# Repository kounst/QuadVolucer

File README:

>QuadVolucer

QuadVolucer is a Quadcopter project basend on the STM32 Microcontroller. It uses a ITG-3200 3-axis gyroskope.

The aim of this project is not to develop a Copter which is as stable as possible but to leave control to the pilot. Therefore control is HH only.
To archive this no ACCs are needed. There is a footprint for a 3-axis ACC on the PCB though. So angular control could be implemented but I'm propably not going to do so.

>canBLC

canBLC is a motor controller for BLDC motors. It is meant to be used with multicopters like the QuadVolucer. As an interface it will support I2C, PWM and of cause high speed CAN.

	status:	- Hardware design is finished 
		- Software basic features working (only CAN support)

	todo:	- extensive testing
		- testing on the QuadVolucer :-)
		- implementation of PWM and I2C interface.

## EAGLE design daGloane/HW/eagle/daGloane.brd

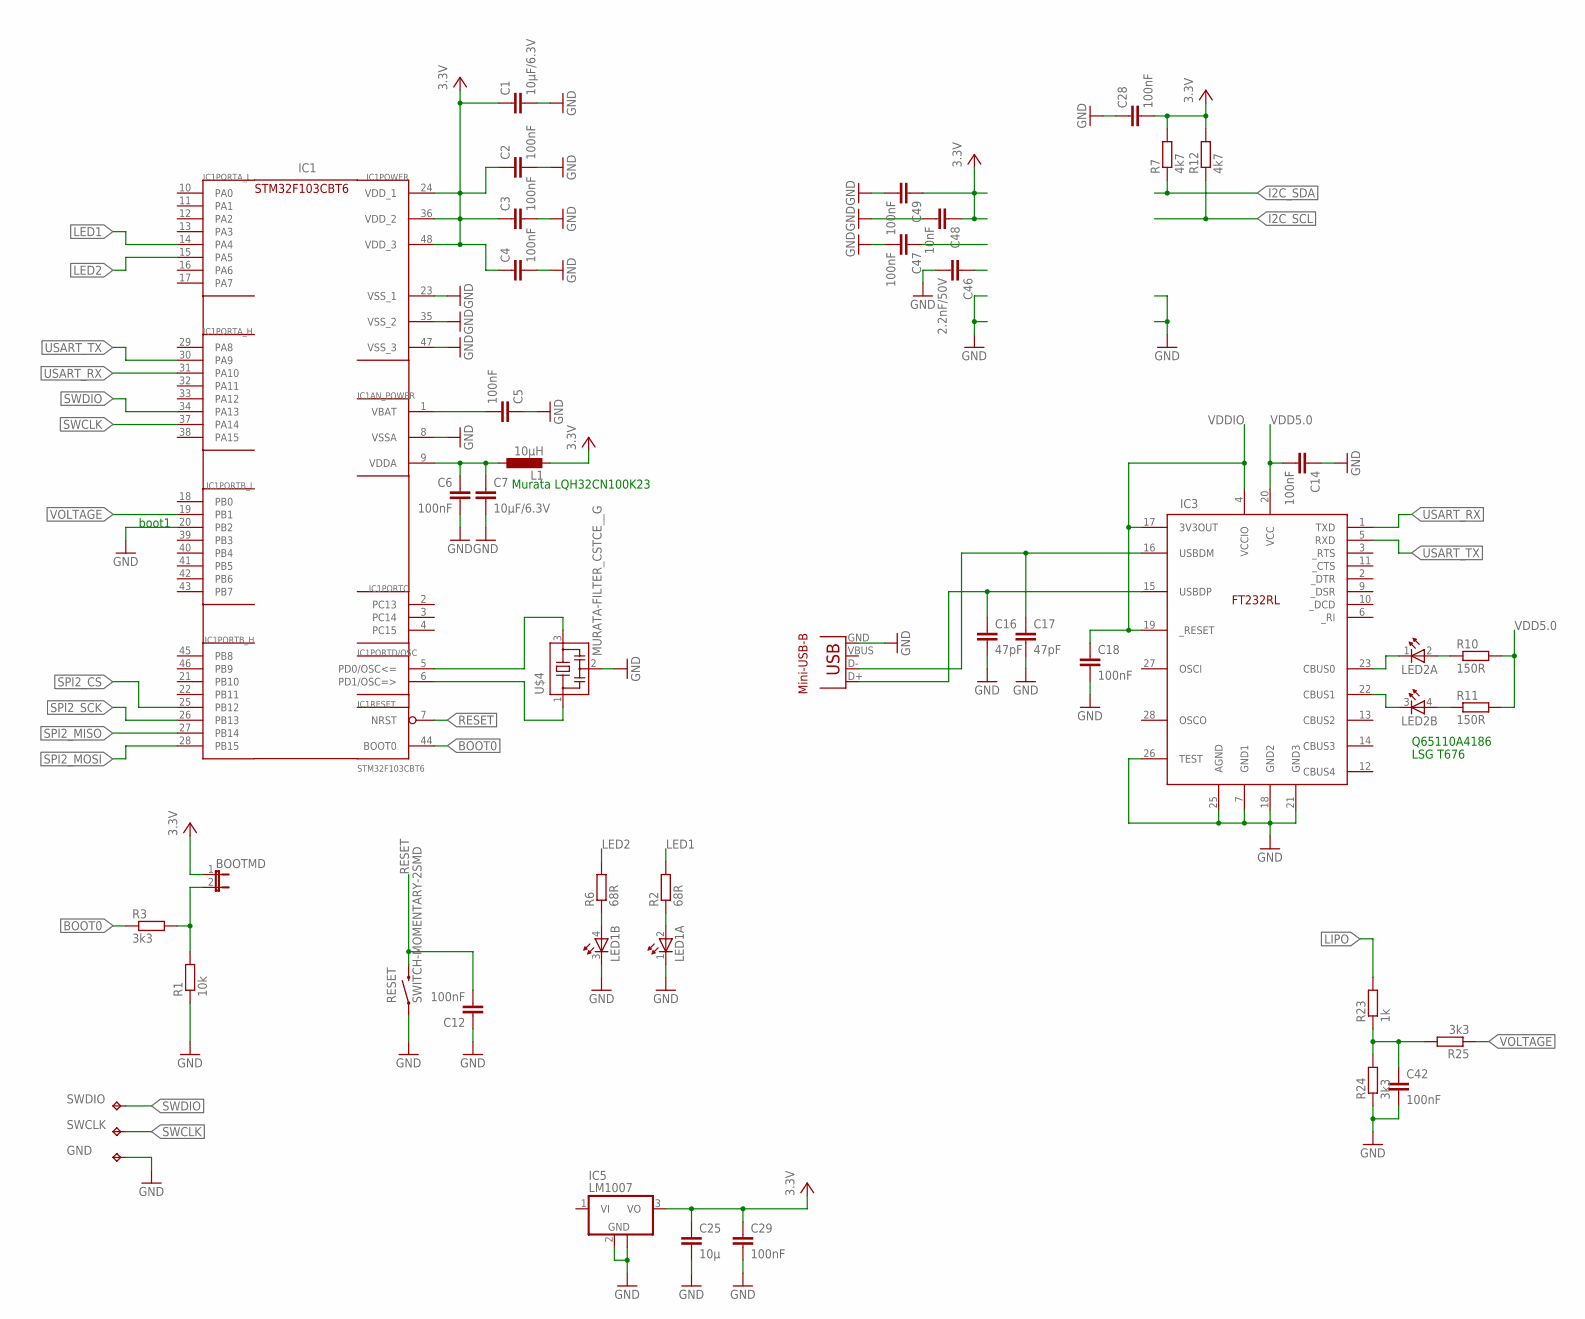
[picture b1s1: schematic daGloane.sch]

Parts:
BOOTMD: JUMPER-2PTH; 1X02
C1, C7: 10µF/6.3V; C0805
C2, C3, C4, C5, C6, C12, C14, C18, C28, C29, C42, C47, C49: 100nF; C0805
C16, C17: 47pF; C0805
C25: 10µ; C0805
C46: 2.2nF/50V; C0805
C48: 10nF; C0805
GND: TESTPAD_TPB1,27; TESTPAD_B1,27
IC1: STM32F103CBT6; TQFP48
IC3: FT232RL; SSOP28DB
IC5: UA78M05DCY; SOT223
L1: 10µH; R1210
LED1, LED2: TOPLED-2-MPI; P-LCC-4-2-MPI
R1: 10k; R0805
R2, R6: 68R; R0805
R3, R24, R25: 3k3; R0805
R7, R12: 4k7; R0805
R10, R11: 150R; R0805
R23: 1k; R0805
RESET: SWITCH-MOMENTARY-2SMD; TACTILE_SWITCH_SMD
SWCLK: TESTPAD_TPB1,27; TESTPAD_B1,27
SWDIO: TESTPAD_TPB1,27; TESTPAD_B1,27
U$4: MURATA-FILTER_CSTCE__G
USB2: USB-MB-S2; USB-MP-S2

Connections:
BOOT0: IC1.44 (BOOT0), R3.1
D+: C16.1, IC3.15 (USBDP), USB2.D+
D-: C17.1, IC3.16 (USBDM), USB2.D-
GND: C1.2, C2.2, C3.2, C4.2, C5.1, C6.2, C7.2, C12.1, C14.1, C16.2, C17.2, C18.2, C25.2, C28.1, C29.2, C42.2, C46.2, C47.2, C48.2, C49.2, GND.PP, IC1.8 (VSSA), IC1.20 (PB2), IC1.23 (VSS_1), IC1.35 (VSS_2), IC1.47 (VSS_3), IC3.7 (GND1), IC3.18 (GND2), IC3.21 (GND3), IC3.25 (AGND), IC3.26 (TEST), IC5.2 (GND), IC5.4 (GND), LED1.1 (C), LED1.3 (C), R1.1, R24.1, RESET.1, U$4.2, USB2.GND
I2C_SCL: R12.1
I2C_SDA: R7.1
LED1: IC1.14 (PA4), R2.2
LED2: IC1.15 (PA5), R6.2
LIPO: R23.2
unnamed: IC3.23 (CBUS0), LED2.1 (C)
unnamed: IC3.22 (CBUS1), LED2.3 (C)
unnamed: LED2.2 (A), R10.1
unnamed: LED2.4 (A), R11.1
unnamed: LED1.2 (A), R2.1
unnamed: LED1.4 (A), R6.1
unnamed: BOOTMD.2, R1.2, R3.2
unnamed: C42.1, R23.1, R24.2, R25.2
RESET: C12.2, IC1.7 (NRST), RESET.3 (2)
SPI2_CS: IC1.25 (PB12)
SPI2_MISO: IC1.27 (PB14)
SPI2_MOSI: IC1.28 (PB15)
SPI2_SCK: IC1.26 (PB13)
SWCLK: IC1.37 (PA14), SWCLK.PP
SWDIO: IC1.34 (PA13), SWDIO.PP
USART_RX: IC1.31 (PA10), IC3.1 (TXD)
USART_TX: IC1.30 (PA9), IC3.5 (RXD)
VBAT: C5.2, IC1.1 (VBAT)
VCC: BOOTMD.1, C1.1, C2.1, C3.1, C4.1, C25.1, C28.2, C29.1, C48.1, C49.1, IC1.24 (VDD_1), IC1.36 (VDD_2), IC1.48 (VDD_3), IC5.3 (VO), L1.2, R7.2, R12.2
VDD5.0: C14.2, IC3.20 (VCC), R10.2, R11.2
VDDA: C6.1, C7.1, IC1.9 (VDDA), L1.1
VDDIO: C18.1, IC3.4 (VCCIO), IC3.17 (3V3OUT), IC3.19 (_RESET)
VOLTAGE: IC1.19 (PB1), R25.1

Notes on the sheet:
STM32F103CBT6
Murata LQH32CN100K23
FT232RL
Mini-USB-B
IC1
LSG T676
Q65110A4186
boot1

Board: 2 copper layers, 44 parts (0 on the bottom side), 25 nets, no tracks yet.

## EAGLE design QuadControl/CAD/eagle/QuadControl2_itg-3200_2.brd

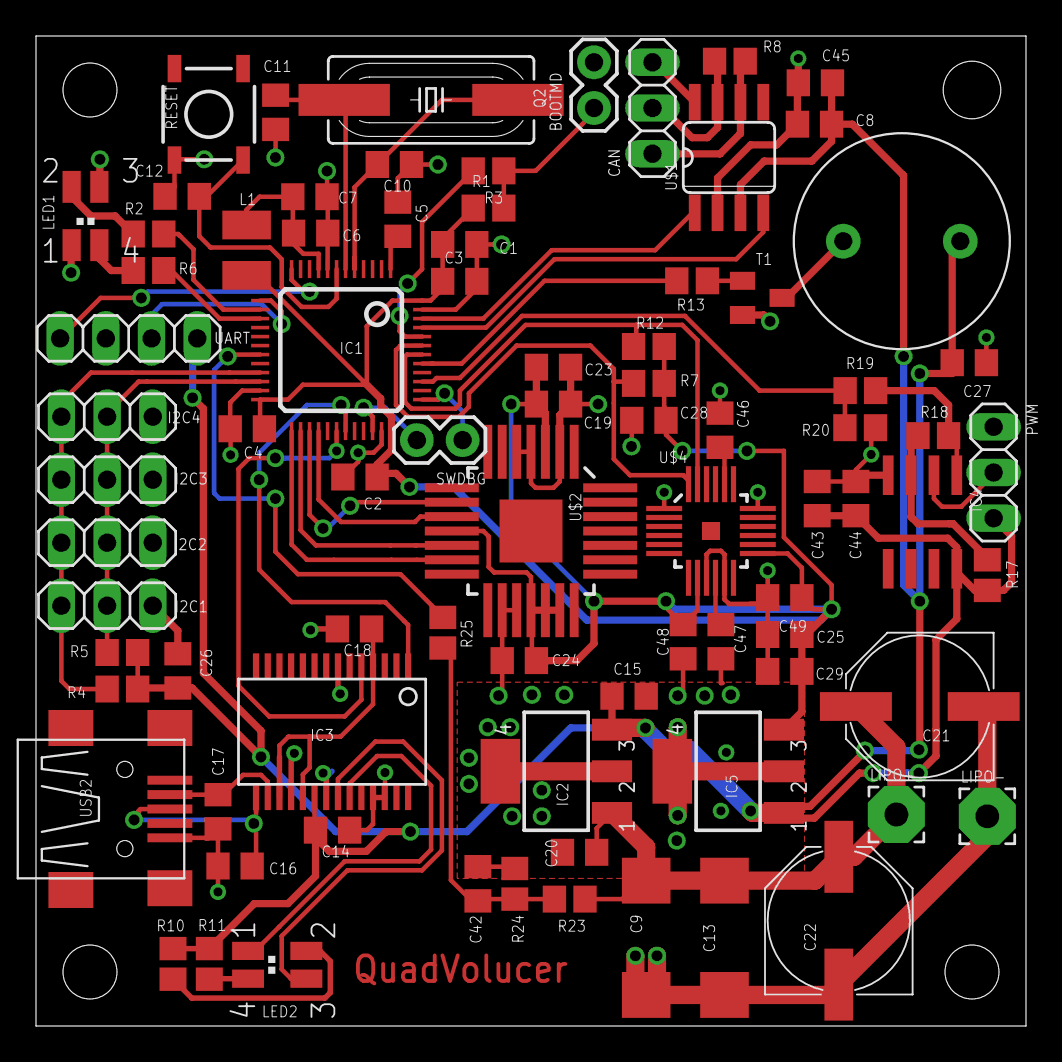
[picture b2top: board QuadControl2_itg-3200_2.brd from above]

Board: 2 copper layers, 55.0 x 55.0 mm, 83 parts (0 on the bottom side), 51 nets.

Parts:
BOOTMD: 1X02
C1, C7: 10µF/6.3V; C0805
C2, C3, C4, C5, C6, C8, C12, C14, C15, C18, C20, C23, C24, C26, C28, C29, C42, C44, C47, C49: 100nF; C0805
C9, C13: 10µ; D/7343-31R
C10, C11: 22pF; C0805
C16, C17: 47pF; C0805
C19, C25: 10µ; C0805
C21, C22: 330µ; PANASONIC_F
C27, C43, C45: 1µ; C0805
C46: 2.2nF/50V; C0805
C48: 10nF; C0805
CAN: 1X03
I2C1, I2C2, I2C3, I2C4: 1X03
IC1: STM32F103CBT6; TQFP48
IC2, IC5: UA78M05DCY; SOT223
IC3: FT232RL; SSOP28DB
IC4: TS912D; SO08
L1: 10µH; R1210
LED1, LED2: P-LCC-4-2-MPI
LIPO+: 3,17/1,3
LIPO-: 3,17/1,3
PWM: 1X03
Q2: 8MHz; SM49
R1: 10k; R0805
R2, R6: 68R; R0805
R3, R13, R25: 3k3; R0805
R4, R5, R7, R12, R24: 4k7; R0805
R8: 120R; R0805
R10, R11: 150R; R0805
R17: 120k; R0805
R18, R20: 33k; R0805
R19: 18k; R0805
R23: 22k; R0805
RESET: SWITCH-MOMENTARY-2SMD; TACTILE_SWITCH_SMD
SWDBG: 1X02
T1: BC847; SOT23
U$1: MCP2551SO8; SO08
U$2: AIS325DQ_DEVICEHANDSOLDER; QFN-28
U$3: SUMMER_DIV; SUMMER_FOOTPRINT
U$4: ITG-3200; QFN-24HANDSOLDER
UART: 1X04
USB2: USB-MB-S2; USB-MP-S2

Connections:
12V_LIPO: C9.+, C13.+, C20.1, C21.+, C22.+, IC2.1, LIPO+.1, R23.2
3243: T1.3, U$3.-
BOOT0: IC1.44, R3.1
CAN_RX: IC1.45, U$1.4
CAN_TX: IC1.46, U$1.1
D+: C16.1, IC3.15, USB2.D+
D-: C17.1, IC3.16, USB2.D-
GND: BOOTMD.2, C1.2, C2.2, C3.2, C4.2, C5.1, C6.2, C7.2, C8.2, C9.-, C10.1, C11.1, C12.1, C13.-, C14.1, C15.2, C16.2, C17.2, C18.2, C19.2, C20.2, C21.-, C22.-, C23.2, C24.2, C25.2, C26.1, C27.1, C28.1, C29.2, C42.2, C43.2, C44.2, C45.2, C46.2, C47.2, C48.2, C49.2, CAN.3, I2C1.1, I2C2.1, I2C3.1, I2C4.1, IC1.8, IC1.23, IC1.35, IC1.47, IC2.2, IC2.4, IC3.7, IC3.18, IC3.21, IC3.25, IC3.26, IC4.4, IC5.2, IC5.4, LED1.1, LED1.3, LIPO-.1, PWM.1, R20.1, R24.1, RESET.1, T1.2, U$1.2, U$1.8, U$2.2, U$2.4, U$2.5, U$2.16, U$2.17, U$4.1, U$4.9, U$4.11, U$4.18, UART.2, USB2.GND
I2C2_SCL: I2C1.3, I2C2.3, I2C3.3, I2C4.3, IC1.21, R4.1
I2C2_SDA: I2C1.2, I2C2.2, I2C3.2, I2C4.2, IC1.22, R5.1
I2C_SCL: IC1.42, R12.1, U$4.23
I2C_SDA: IC1.43, R7.1, U$4.24
unnamed: CAN.1, R8.2, U$1.6
unnamed: IC3.23, LED2.1
unnamed: IC3.22, LED2.3
unnamed: LED2.2, R10.1
unnamed: LED2.4, R11.1
unnamed: C46.1, U$4.20
unnamed: CAN.2, R8.1, U$1.7
unnamed: LED1.2, R2.1
unnamed: LED1.4, R6.1
unnamed: BOOTMD.1, R1.1, R3.2
unnamed: R13.1, T1.1
unnamed: C47.1, U$4.10
unnamed: C10.2, IC1.5, Q2.2
unnamed: C11.2, IC1.6, Q2.1
unnamed: C42.1, R23.1, R24.2, R25.2
unnamed: IC4.3, R17.2, R18.1
unnamed: IC4.1, R18.2, R19.1
PA4: IC1.14, R2.2
PA5: IC1.15, R6.2
PWM_CC: IC1.39, R19.2, R20.2
PWM_IN: IC4.2, PWM.2
RC_UART_RX: IC1.12, UART.1
RC_UART_TX: IC1.13, UART.3
RESET: C12.2, IC1.7, RESET.3
SPI2_CS: IC1.25, U$2.13
SPI2_MISO: IC1.27, U$2.9
SPI2_MOSI: IC1.28, U$2.10
SPI2_SCK: IC1.26, U$2.12
SUMMER: IC1.41, R13.2
SWCLK: IC1.37, SWDBG.1
SWDIO: IC1.34, SWDBG.2
USART_RX: IC1.31, IC3.1
USART_TX: IC1.30, IC3.5
VBAT: C5.2, IC1.1
VDD3.3: C1.1, C2.1, C3.1, C4.1, C19.1, C23.1, C24.1, C25.1, C28.2, C29.1, C48.1, C49.1, IC1.24, IC1.36, IC1.48, IC5.3, L1.2, R1.2, R7.2, R12.2, U$2.3, U$2.11, U$2.18, U$2.19, U$2.20, U$4.8, U$4.13
VDD5.0: C8.1, C14.2, C15.1, C26.2, C27.2, C43.1, C44.1, C45.1, IC2.3, IC3.20, IC4.8, IC5.1, PWM.3, R4.2, R5.2, R10.2, R11.2, R17.1, U$1.3, U$3.+, UART.4
VDDA: C6.1, C7.1, IC1.9, L1.1
VDDIO: C18.1, IC3.4, IC3.17, IC3.19
VOLTAGE: IC1.19, R25.1

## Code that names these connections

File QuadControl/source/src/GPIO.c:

// Header: 		IO Port Configuation
// File Name: GPIO.c
// Author: 		Konstantin Reichmeyer
// Date:   		13.11.10


/* Includes ------------------------------------------------------------------*/
#include "stm32f10x.h"
#include "GPIO.h"


void GPIO_Configuration(void)
{
  GPIO_InitTypeDef GPIO_InitStructure;

  /* GPIOB Configuration: LED1 & LED2 */
  GPIO_InitStructure.GPIO_Pin = LED1_PIN;
  GPIO_InitStructure.GPIO_Mode = GPIO_Mode_Out_PP;
  GPIO_InitStructure.GPIO_Speed = GPIO_Speed_50MHz;
  GPIO_Init(LED1_GPIO_PORT, &GPIO_InitStructure);

  GPIO_InitStructure.GPIO_Pin = LED2_PIN;
  GPIO_Init(LED2_GPIO_PORT, &GPIO_InitStructure);

  /* Configuration: SUMMER pin PB5*/
  GPIO_InitStructure.GPIO_Pin = SUMMER_PIN;
  GPIO_InitStructure.GPIO_Mode = GPIO_Mode_Out_PP;
  GPIO_InitStructure.GPIO_Speed = GPIO_Speed_50MHz;
  GPIO_Init(SUMMER_GPIO_PORT, &GPIO_InitStructure);

  /* Configuration Voltage pin PB1 */
  GPIO_InitStructure.GPIO_Pin = GPIO_Pin_1;
  GPIO_InitStructure.GPIO_Mode = GPIO_Mode_AIN;
  GPIO_InitStructure.GPIO_Speed = GPIO_Speed_50MHz;
  GPIO_Init(GPIOB, &GPIO_InitStructure);

  /* Configure USART1 Tx (PA9) as alternate function push-pull */
  GPIO_InitStructure.GPIO_Pin = GPIO_Pin_9;
  GPIO_InitStructure.GPIO_Speed = GPIO_Speed_2MHz;
  GPIO_InitStructure.GPIO_Mode = GPIO_Mode_AF_PP;
  GPIO_Init(GPIOA, &GPIO_InitStructure);

  /* Configure USART1 Rx (PA10), USART2 RX (PA3) as input floating */
  GPIO_InitStructure.GPIO_Pin = GPIO_Pin_10 | GPIO_Pin_3;
  GPIO_InitStructure.GPIO_Mode = GPIO_Mode_IN_FLOATING;
  GPIO_Init(GPIOA, &GPIO_InitStructure);


  /* Configure I2C1 pins: SCL and SDA */
  GPIO_InitStructure.GPIO_Pin =  GPIO_Pin_6 | GPIO_Pin_7;
  GPIO_InitStructure.GPIO_Speed = GPIO_Speed_50MHz;
  GPIO_InitStructure.GPIO_Mode = GPIO_Mode_AF_OD;
  GPIO_Init(GPIOB, &GPIO_InitStructure);

#ifndef CAN_blc
  /* Configure I2C2 pins: SCL and SDA */
  GPIO_InitStructure.GPIO_Pin =  GPIO_Pin_10 | GPIO_Pin_11;
  GPIO_InitStructure.GPIO_Speed = GPIO_Speed_50MHz;
  GPIO_InitStructure.GPIO_Mode = GPIO_Mode_AF_OD;
  GPIO_Init(GPIOB, &GPIO_InitStructure);
#endif

#ifdef CAN_blc
  /* Configure CAN pin: RX */
  GPIO_InitStructure.GPIO_Pin = GPIO_Pin_8;
  GPIO_InitStructure.GPIO_Mode = GPIO_Mode_IPU;
  GPIO_Init(GPIOB, &GPIO_InitStructure);
  
  /* Configure CAN pin: TX */
  GPIO_InitStructure.GPIO_Pin = GPIO_Pin_9;
  GPIO_InitStructure.GPIO_Mode = GPIO_Mode_AF_PP;
  GPIO_InitStructure.GPIO_Speed = GPIO_Speed_50MHz;
  GPIO_Init(GPIOB, &GPIO_InitStructure);

  GPIO_PinRemapConfig(GPIO_Remap1_CAN1 , ENABLE);
#endif


/* Enable I2C1 reset state */
  RCC_APB1PeriphResetCmd(RCC_APB1Periph_I2C1, ENABLE);
/* Release I2C1 from reset state */
  RCC_APB1PeriphResetCmd(RCC_APB1Periph_I2C1, DISABLE);

#ifndef CAN_blc
  /* Enable I2C2 reset state */
  RCC_APB1PeriphResetCmd(RCC_APB1Periph_I2C2, ENABLE);
/* Release I2C2 from reset state */
  RCC_APB1PeriphResetCmd(RCC_APB1Periph_I2C2, DISABLE);
#endif

}


const uint16_t GPIO_PIN[3] = {LED1_PIN, LED2_PIN, SUMMER_PIN};
GPIO_TypeDef* GPIO_PORT[3] = {LED1_GPIO_PORT, LED2_GPIO_PORT, SUMMER_GPIO_PORT};


/**
  * @brief  Toggles the selected LED.
  * @param  Led: Specifies the Led to be toggled. 
  *   This parameter can be one of following parameters:
  *     @arg LED1
  *     @arg LED2 
  * @retval None
  */
void QuadC_LEDToggle(Led_TypeDef Led)
{
  GPIO_PORT[Led]->ODR ^= GPIO_PIN[Led];
}

/**
  * @brief  Turns selected LED On.
  * @param  Led: Specifies the Led to be set on. 
  *   This parameter can be one of following parameters:
  *     @arg LED1
  *     @arg LED2
  * @retval None
  */
void QuadC_LEDOn(Led_TypeDef Led)
{
  GPIO_PORT[Led]->BSRR = GPIO_PIN[Led];     
}

/**
  * @brief  Turns selected LED Off.
  * @param  Led: Specifies the Led to be set off. 
  *   This parameter can be one of following parameters:
  *     @arg LED1
  *     @arg LED2
  * @retval None
  */
void QuadC_LEDOff(Led_TypeDef Led)
{
  GPIO_PORT[Led]->BRR = GPIO_PIN[Led];  
}

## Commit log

2011-06-17 commit readme
2011-06-17 initial commit :zz
2011-06-17 CAD files copter frame added
2011-06-18 position of RC receiver changed
2011-06-18 Size of Centerplate increased
    batteriebox removed -> space for battery inbetween of centerplates.
2011-06-19 inital commit of schematic and layout
2011-06-19 pockets added to centerplates to reduce weight
2011-06-19 pockets in centerplate modified
2011-06-19 minor changes + cleand up + new rendered image of copter
2011-06-20 space for batterie increased
2011-07-02 added rs232 communication with gui
2011-07-03 minor bug fix in uart gui communication rc and gyro calibration is now only being done if last reset was a powerdown reset
2011-07-03 rs232 gui communication improved: pid parameter can be programmed using the gui
2011-07-05 more parameters can be modified using the gui: new are idle_throttle and batterie warnung voltage
2011-07-06 gyros direction can be inverted using the gui
2011-07-06 Information about the project added
2011-07-10 minor change to statemachine state changeing criteria some cleaning
2011-07-10 obj files deleted
2011-07-10 lst files deleted
2011-08-29 Initial commit of canBLC canBLC is a controller for BLDC motors which communicates via the CAN-Bus. It also supports I2C and PWM.
2011-08-29 minor change
2011-09-02 Changed diode of bootstraping circuit of gate drivers circuit
2011-09-02 files moved
2011-09-02 added text about canBLC
2011-09-02 status of canBLC added
2011-09-02 png images of QuadControl schematic and layout added
2011-09-02 LED package changed
2011-09-02 missing trace fixed
2011-09-04 license information added
2011-09-04 license imformation added
2011-09-04 minor correction
2011-09-04 duplicate content
2011-09-17 stop mask on vias removed
2011-09-17 Incorrect footprint of resonator replaced
2011-09-22 values of voltage divider for switch mode regulator changed
2011-10-03 vias added to solder pads to improve mechanical strength
2011-10-03 minor layout change
2011-10-03 photo of first prototype added
2011-10-03 orientation of photos corrected
2011-10-23 support for CANblc added - not properly tested jet
2011-10-23 canBLC project status updated
2011-10-24 current protection implemented
2011-10-27 eeprom emultion implemented: canBLC address, timing and limit settings can be saved permanently
2011-10-31 new song added
2011-11-01 startup routine improved
2011-11-01 compiler switch introduced to enable/disable current protection
2011-11-06 CAN speed message timeout can be set via CAN config message and saved in the flash memory
2011-11-06 canBLC CAN Protokoll description - german only
2011-11-06 moved into canBLC project directory
2011-11-06 status update
2011-11-26 header cleaned up
2011-11-26 can config frame table corrected
2012-01-25 Initial commit of BOM BOM may be inconsistent with schematic, Labels (C1, R, .. ) are correct though
2012-01-25 Information for Ceramic Resonator added
2012-02-12 two step positioning for startup
2012-03-18 inconsistency with schematic solved
2012-03-18 support for Multiplex m-link serial servo data interface (B/D) implemented scaling of input data needs to be done
2012-03-18 New function to check whether TX stick is in a certain position
2012-03-21 Scaling of MPX receiver input data
2012-03-22 comments added
2012-04-22 adapted shresholds for state changes of FSM to MPX M-LINK receivers data
2012-04-22 GPIO configuration cleaned up
2012-04-28 dicke des Motorträger erhöht um Eigenresonanzfrequenz der Trager zu erhöhen.
2012-04-28 Bohrung für 35MHz Antenne entfernt
2012-04-28 useless commented code removed
2012-04-30 ITG-3200 init routine implemented
2012-05-01 low pass filtering of differential term added
2012-05-01 ITG-3200 initalization added. Befor this it was running outside of its specified operation conditions. 250°/s instead of 2000°/s Datasheet: " Set to 03h for proper operation."
2012-05-01 edge frequency of gyros internal low pass filter changed from 256Hz to 98Hz
2012-05-01 somehow some of the lastest history was deleted from the reposistory.. ->recommit
2012-05-10 Inital commit of daGloane schematic
2012-05-10 info about daGloane added
2012-05-11 moved to recository of its own: https://github.com/kounst/daGloane
2012-05-13 Some comments added
2012-05-13 As the canBLC project is on hold I disabled the CAN interface
2012-05-13 comments added unused code removed
2012-05-17 yaw scaling adapted
2012-05-17 section about daGloane removed. It has moved to a severate repository: https://github.com/kounst/daGloane
2012-05-17 README renamed for test markup
2012-05-17 broken I term of yaw controller fixed
2012-05-17 stick sensitivity which was hardcoded so far can now be set using the TriGUI
2012-05-24 inital commit of required libs
2023-08-26 flash content of the MCU dumped: flashDump_20230826.bin Code is compiling in Keil MDK with ARM_Compiler_5.06u7
2023-08-26 cross talk bug of D part of PID controllers fixed
